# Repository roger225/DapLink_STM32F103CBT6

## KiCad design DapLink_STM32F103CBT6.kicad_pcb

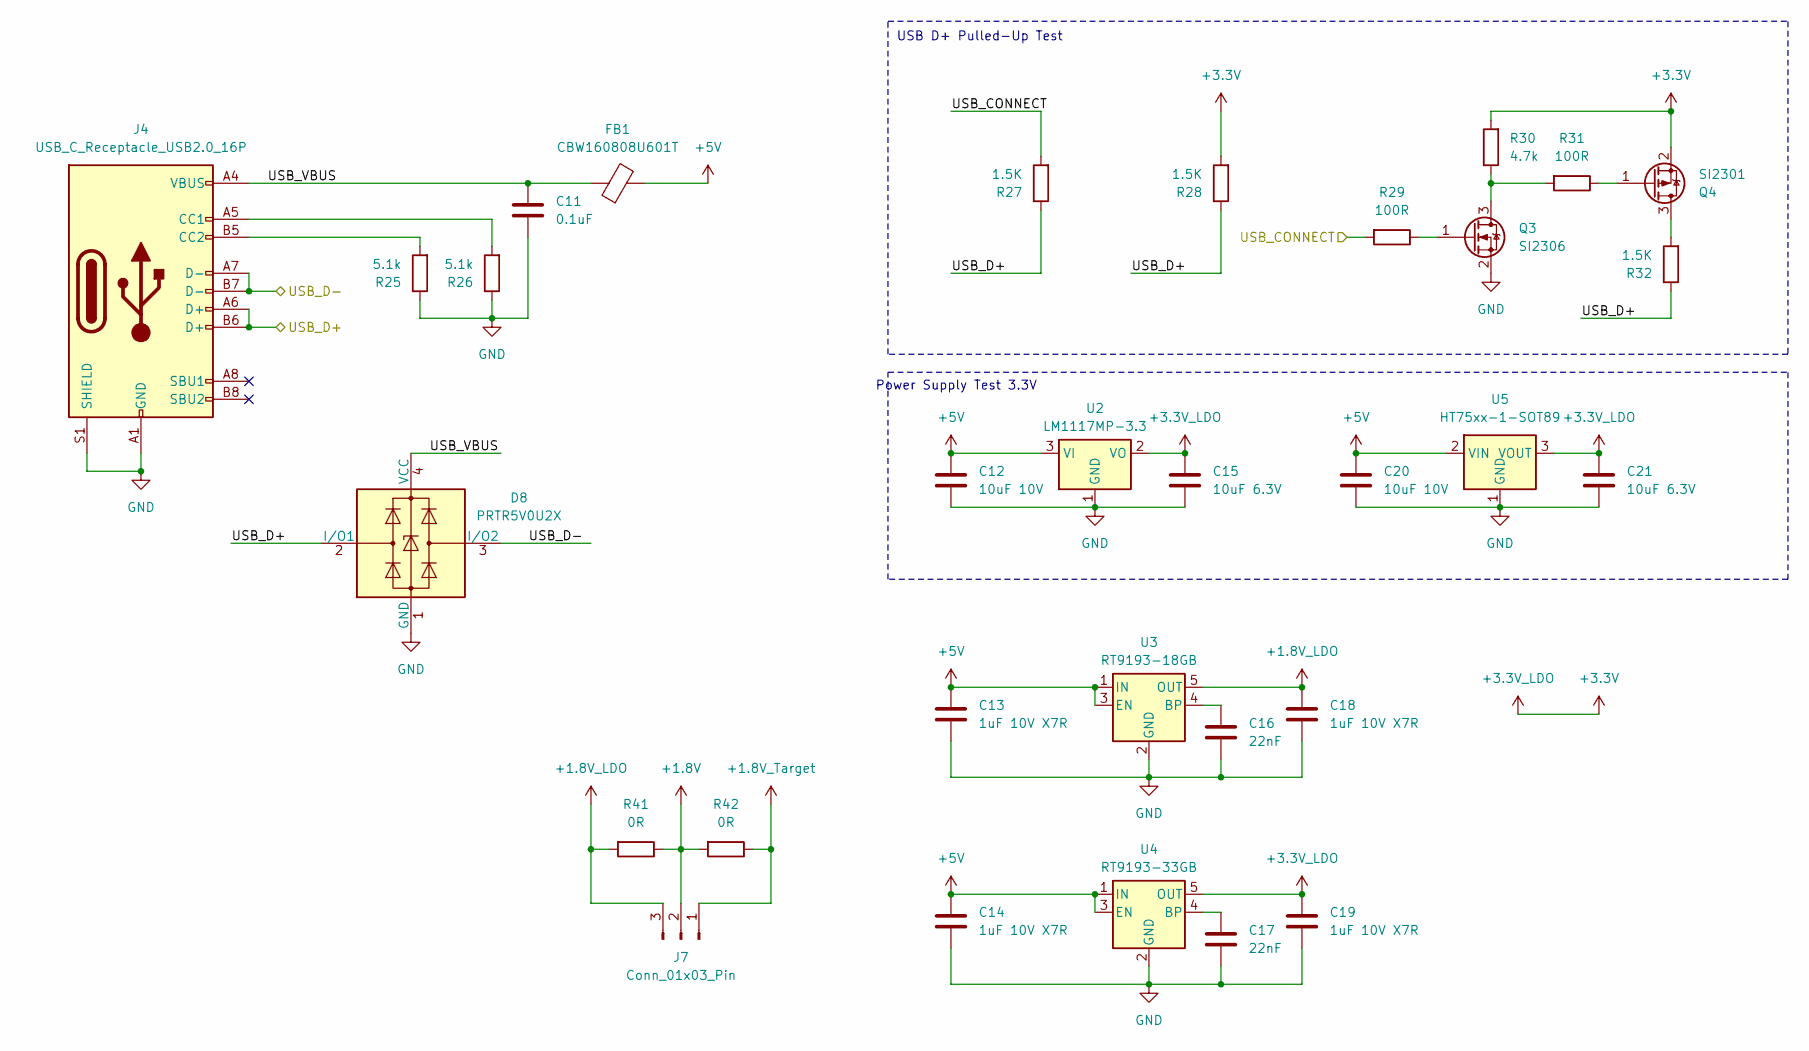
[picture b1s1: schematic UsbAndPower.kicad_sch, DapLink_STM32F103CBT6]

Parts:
C11: 0.1uF; C_0805_2012Metric
C12, C20: 10uF 10V; C_0805_2012Metric
C13, C14, C18, C19: 1uF 10V X7R; C_1206_3216Metric
C15, C21: 10uF 6.3V; C_0805_2012Metric
C16, C17: 22nF; C_0805_2012Metric
D8: PRTR5V0U2X; SOT-143
FB1: CBW160808U601T; L_0603_1608Metric
J4: USB_C_Receptacle_USB2.0_16P; USB_C_Receptacle_G-Switch_GT-USB-7010ASV
J7: Conn_01x03_Pin; PinHeader_1x03_P2.54mm_Vertical
Q3: SI2306; SOT-23
Q4: SI2301; SOT-23
R25, R26: 5.1k; R_0805_2012Metric
R27, R28, R32: 1.5K; R_0805_2012Metric
R29, R31: 100R; R_0805_2012Metric
R30: 4.7k; R_0805_2012Metric
R41, R42: 0R; R_0805_2012Metric
U2: LM1117MP-3.3; SOT-223-3_TabPin2
U3: RT9193-18GB; SOT-23-5
U4: RT9193-33GB; SOT-23-5
U5: HT75xx-1-SOT89; SOT-89-3

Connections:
+1.8V: J7.2, R41.1, R42.2; also elsewhere on the board
+1.8V_LDO: C18.1, J7.3, R41.2, U3.5 (OUT)
+1.8V_Target: J7.1, R42.1; also elsewhere on the board
+3.3V: C15.1, C19.1, C21.1, Q4.2 (S), R28.2, R30.2, U2.2 (VO), U4.5 (OUT), U5.3 (VOUT); also elsewhere on the board
+5V: C12.1, C13.1, C14.1, C20.1, FB1.2, U2.3 (VI), U3.1 (IN), U3.3 (EN), U4.1 (IN), U4.3 (EN), U5.2 (VIN)
/UsbAndPower/USB_CONNECT: R27.2, R29.2; also elsewhere on the board
/UsbAndPower/USB_D+: D8.2 (I/O1), J4.A6 (D+), J4.B6 (D+), R27.1, R28.1, R32.1; also elsewhere on the board
/UsbAndPower/USB_D-: D8.3 (I/O2), J4.A7 (D-), J4.B7 (D-); also elsewhere on the board
/UsbAndPower/USB_VBUS: C11.1, D8.4 (VCC), FB1.1, J4.A4 (VBUS), J4.A9 (VBUS), J4.B4 (VBUS), J4.B9 (VBUS)
GND: C11.2, C12.2, C13.2, C14.2, C15.2, C16.2, C17.2, C18.2, C19.2, C20.2, C21.2, D8.1 (GND), J4.A1 (GND), J4.A12 (GND), J4.B1 (GND), J4.B12 (GND), J4.S1 (SHIELD), Q3.2 (S), R25.1, R26.1, U2.1 (GND), U3.2 (GND), U4.2 (GND), U5.1 (GND); also elsewhere on the board
unnamed: J4.A5 (CC1), R26.2
unnamed: J4.B5 (CC2), R25.2
unnamed: Q3.3 (D), R30.1, R31.2
unnamed: Q3.1 (G), R29.1
unnamed: Q4.3 (D), R32.2
unnamed: Q4.1 (G), R31.1
unnamed: C16.1, U3.4 (BP)
unnamed: C17.1, U4.4 (BP)

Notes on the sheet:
Power Supply Test 3.3V
USB D+ Pulled-Up Test

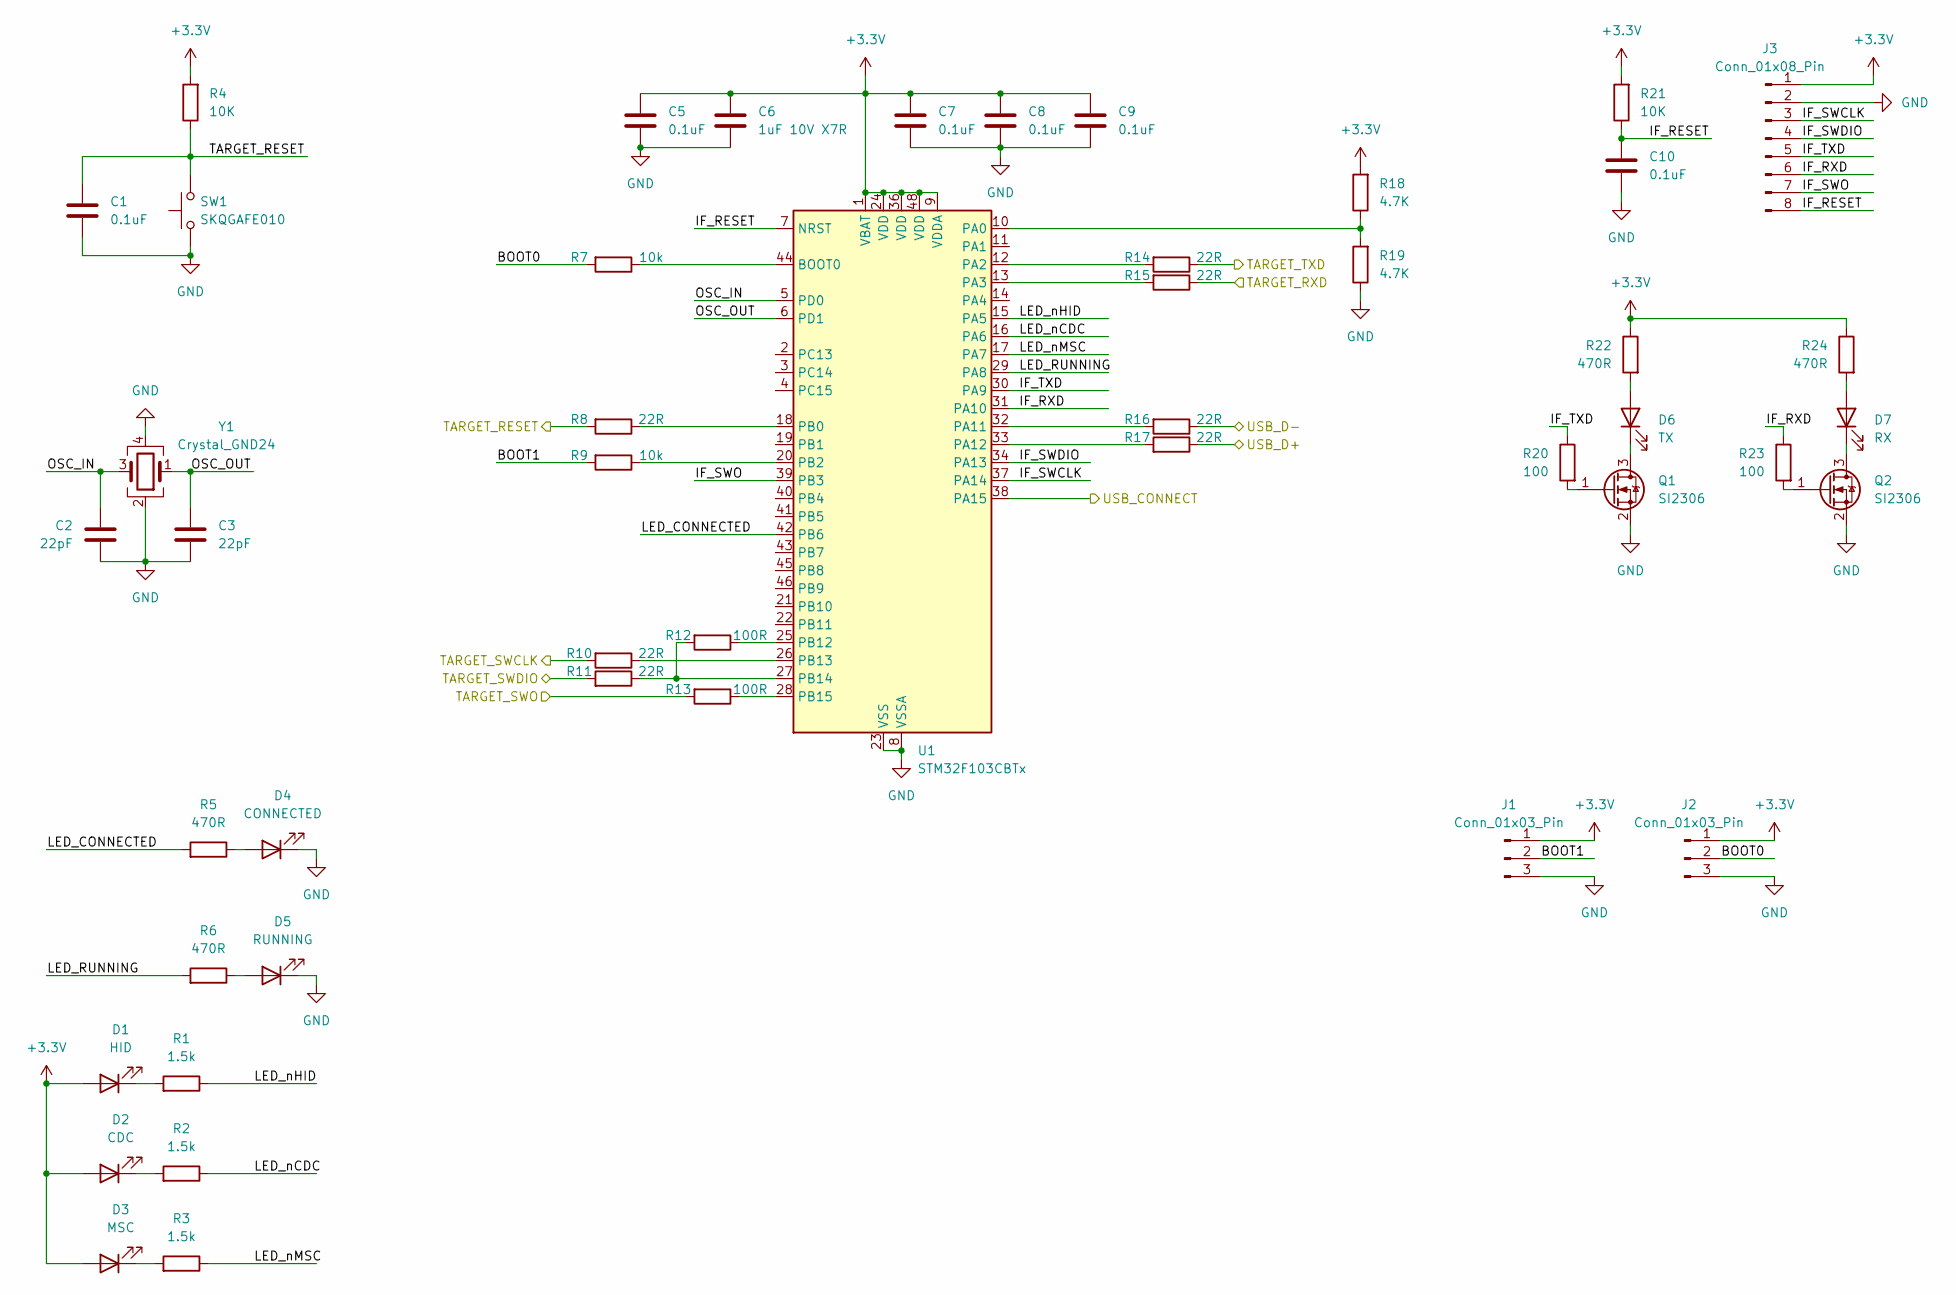
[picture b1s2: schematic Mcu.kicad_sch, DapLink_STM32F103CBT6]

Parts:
C1, C5, C7, C8, C9, C10: 0.1uF; C_0805_2012Metric
C2, C3: 22pF; C_0603_1608Metric
C6: 1uF 10V X7R; C_1206_3216Metric
D1: HID; LED_0805_2012Metric
D2: CDC; LED_0805_2012Metric
D3: MSC; LED_0805_2012Metric
D4: CONNECTED; LED_0805_2012Metric
D5: RUNNING; LED_0805_2012Metric
D6: TX; LED_0805_2012Metric
D7: RX; LED_0805_2012Metric
J1, J2: Conn_01x03_Pin; PinHeader_1x03_P2.54mm_Vertical
J3: Conn_01x08_Pin; PinHeader_1x08_P2.54mm_Vertical
Q1, Q2: SI2306; SOT-23
R1, R2, R3: 1.5k; R_0805_2012Metric
R4, R21: 10K; R_0805_2012Metric
R5, R6, R22, R24: 470R; R_0805_2012Metric
R7, R9: 10k; R_0805_2012Metric
R8, R10, R11, R14, R15, R16, R17: 22R; R_0805_2012Metric
R12, R13: 100R; R_0805_2012Metric
R18, R19: 4.7K; R_0805_2012Metric
R20, R23: 100; R_0805_2012Metric
SW1: SKQGAFE010; SW_SPST_SKQG_WithStem
U1: STM32F103CBTx; LQFP-48_7x7mm_P0.5mm
Y1: Crystal_GND24; Crystal_SMD_3225-4Pin_3.2x2.5mm

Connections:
+3.3V: C5.1, C6.1, C7.1, C8.1, C9.1, D1.2 (A), D2.2 (A), D3.2 (A), J1.1, J2.1, J3.1, R4.2, R18.2, R21.2, R22.1, R24.1, U1.1 (VBAT), U1.9 (VDDA), U1.24 (VDD), U1.36 (VDD), U1.48 (VDD); also elsewhere on the board
/DebugAndUart/TARGET_RESET: C1.1, R4.1, R8.2, SW1.2; also elsewhere on the board
/DebugAndUart/TARGET_RXD: R15.1; also elsewhere on the board
/DebugAndUart/TARGET_SWCLK: R10.2; also elsewhere on the board
/DebugAndUart/TARGET_SWDIO: R11.2; also elsewhere on the board
/DebugAndUart/TARGET_SWO: R13.2; also elsewhere on the board
/DebugAndUart/TARGET_TXD: R14.1; also elsewhere on the board
/Mcu/BOOT0: J2.2, R7.2
/Mcu/BOOT1: J1.2, R9.2
/Mcu/IF_RESET: C10.1, J3.8, R21.1, U1.7 (NRST)
/Mcu/IF_RXD: J3.6, R23.1, U1.31 (PA10)
/Mcu/IF_SWCLK: J3.3, U1.37 (PA14)
/Mcu/IF_SWDIO: J3.4, U1.34 (PA13)
/Mcu/IF_SWO: J3.7, U1.39 (PB3)
/Mcu/IF_TXD: J3.5, R20.1, U1.30 (PA9)
/Mcu/LED_CONNECTED: R5.2, U1.42 (PB6)
/Mcu/LED_RUNNING: R6.2, U1.29 (PA8)
/Mcu/LED_nCDC: R2.1, U1.16 (PA6)
/Mcu/LED_nHID: R1.1, U1.15 (PA5)
/Mcu/LED_nMSC: R3.1, U1.17 (PA7)
/Mcu/OSC_IN: C2.2, U1.5 (PD0), Y1.3
/Mcu/OSC_OUT: C3.1, U1.6 (PD1), Y1.1
/UsbAndPower/USB_CONNECT: U1.38 (PA15); also elsewhere on the board
/UsbAndPower/USB_D+: R17.1; also elsewhere on the board
/UsbAndPower/USB_D-: R16.1; also elsewhere on the board
GND: C1.2, C2.1, C3.2, C5.2, C6.2, C7.2, C8.2, C9.2, C10.2, D4.1 (K), D5.1 (K), J1.3, J2.3, J3.2, Q1.2 (S), Q2.2 (S), R19.1, SW1.1, U1.8 (VSSA), U1.23 (VSS), U1.35 (VSS), U1.47 (VSS), Y1.2, Y1.4; also elsewhere on the board
unnamed: D1.1 (K), R1.2
unnamed: D2.1 (K), R2.2
unnamed: D3.1 (K), R3.2
unnamed: D4.2 (A), R5.1
unnamed: D5.2 (A), R6.1
unnamed: D6.2 (A), R22.2
unnamed: D6.1 (K), Q1.3 (D)
unnamed: D7.2 (A), R24.2
unnamed: D7.1 (K), Q2.3 (D)
unnamed: Q1.1 (G), R20.2
unnamed: Q2.1 (G), R23.2
unnamed: R7.1, U1.44 (BOOT0)
unnamed: R18.1, R19.2, U1.10 (PA0)
unnamed: R14.2, U1.12 (PA2)
unnamed: R15.2, U1.13 (PA3)
unnamed: R16.2, U1.32 (PA11)
unnamed: R17.2, U1.33 (PA12)
unnamed: R8.1, U1.18 (PB0)
unnamed: R9.1, U1.20 (PB2)
unnamed: R12.1, U1.25 (PB12)
unnamed: R10.1, U1.26 (PB13)
unnamed: R11.1, R12.2, U1.27 (PB14)
unnamed: R13.1, U1.28 (PB15)

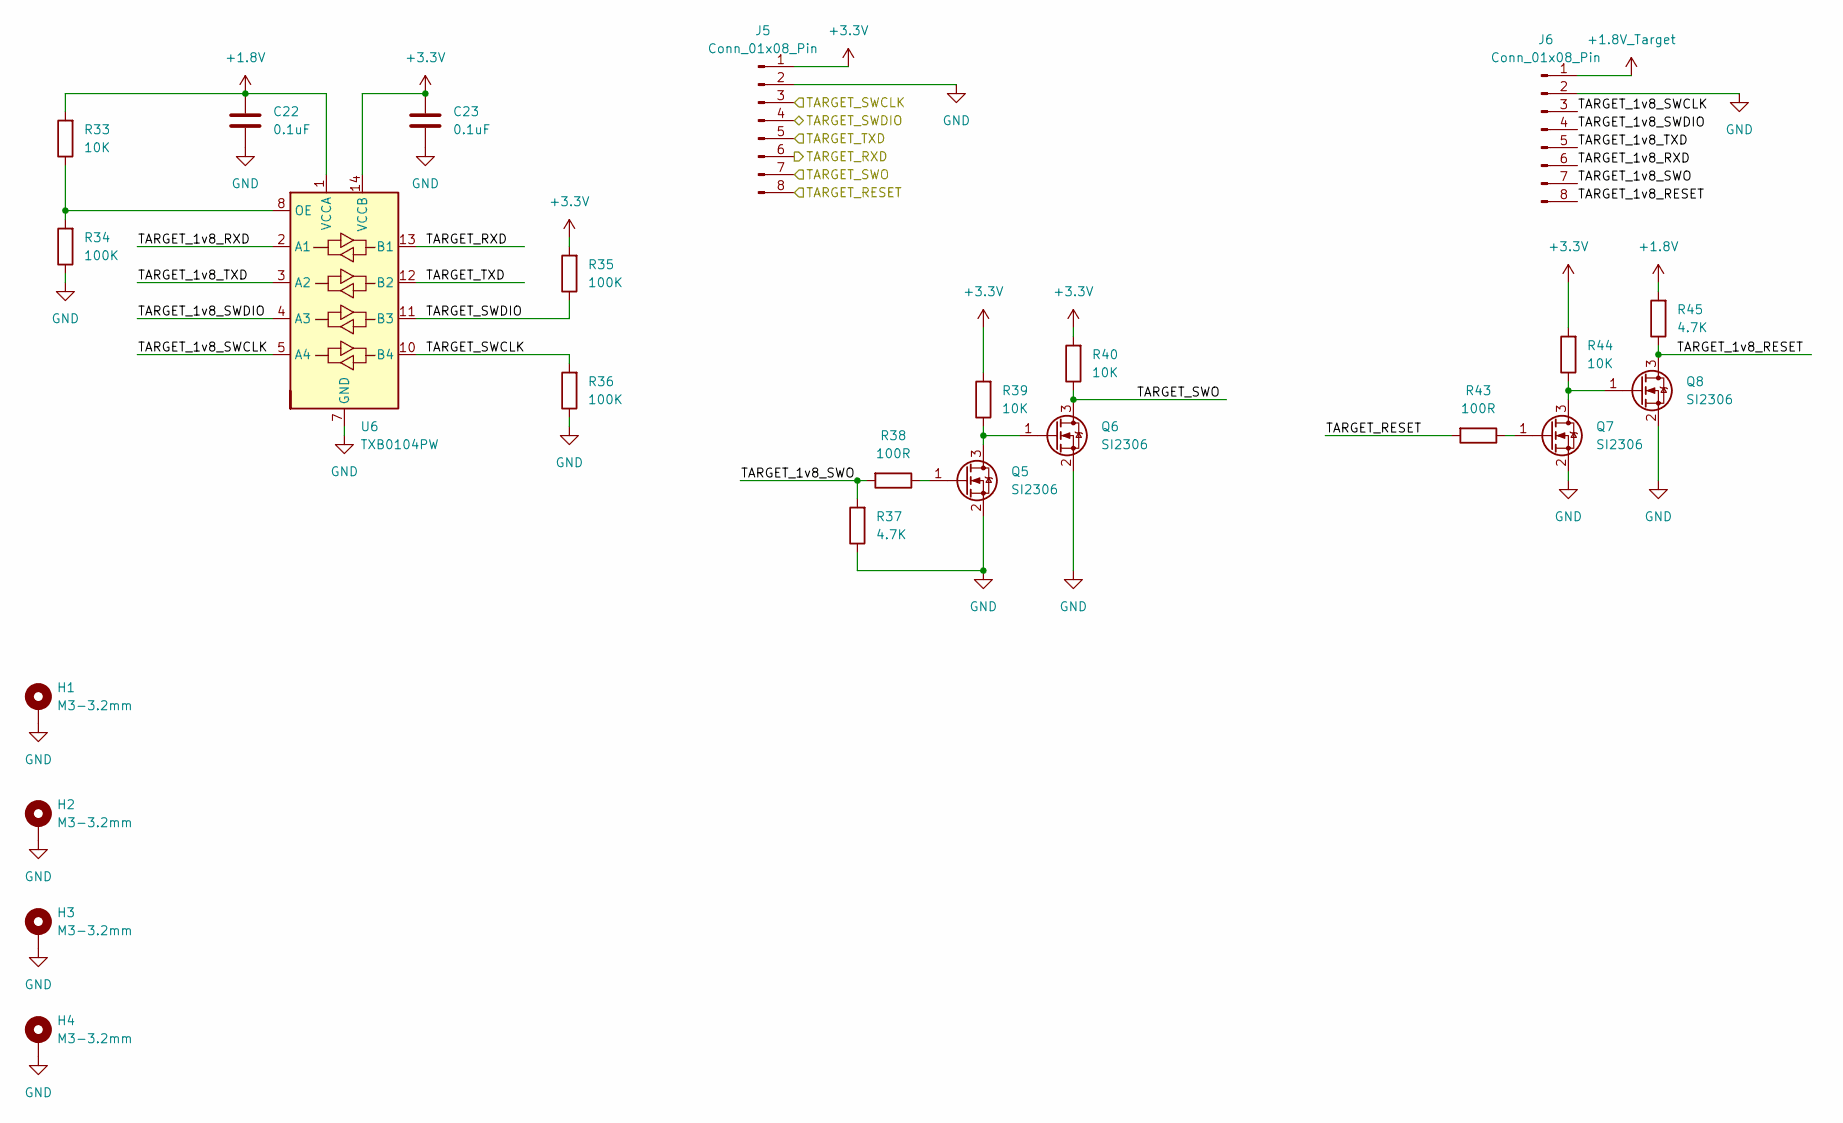
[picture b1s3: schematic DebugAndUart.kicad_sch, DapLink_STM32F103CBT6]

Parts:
C22, C23: 0.1uF; C_0805_2012Metric
H1, H2, H3, H4: M3-3.2mm; MountingHole_3.2mm_M3_Pad_Via
J5, J6: Conn_01x08_Pin; PinHeader_1x08_P2.54mm_Vertical
Q5, Q6, Q7, Q8: SI2306; SOT-23
R33, R39, R40, R44: 10K; R_0805_2012Metric
R34, R35, R36: 100K; R_0805_2012Metric
R37, R45: 4.7K; R_0805_2012Metric
R38, R43: 100R; R_0805_2012Metric
U6: TXB0104PW; TSSOP-14_4.4x5mm_P0.65mm

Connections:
+1.8V: C22.1, R33.2, R45.2, U6.1 (VCCA); also elsewhere on the board
+1.8V_Target: J6.1; also elsewhere on the board
+3.3V: C23.1, J5.1, R35.2, R39.2, R40.2, R44.2, U6.14 (VCCB); also elsewhere on the board
/DebugAndUart/TARGET_1v8_RESET: J6.8, Q8.3 (D), R45.1
/DebugAndUart/TARGET_1v8_RXD: J6.6, U6.2 (A1)
/DebugAndUart/TARGET_1v8_SWCLK: J6.3, U6.5 (A4)
/DebugAndUart/TARGET_1v8_SWDIO: J6.4, U6.4 (A3)
/DebugAndUart/TARGET_1v8_SWO: J6.7, R37.2, R38.2
/DebugAndUart/TARGET_1v8_TXD: J6.5, U6.3 (A2)
/DebugAndUart/TARGET_RESET: J5.8, R43.2; also elsewhere on the board
/DebugAndUart/TARGET_RXD: J5.6, U6.13 (B1); also elsewhere on the board
/DebugAndUart/TARGET_SWCLK: J5.3, R36.2, U6.10 (B4); also elsewhere on the board
/DebugAndUart/TARGET_SWDIO: J5.4, R35.1, U6.11 (B3); also elsewhere on the board
/DebugAndUart/TARGET_SWO: J5.7, Q6.3 (D), R40.1; also elsewhere on the board
/DebugAndUart/TARGET_TXD: J5.5, U6.12 (B2); also elsewhere on the board
GND: C22.2, C23.2, H1.1, H2.1, H3.1, H4.1, J5.2, J6.2, Q5.2 (S), Q6.2 (S), Q7.2 (S), Q8.2 (S), R34.1, R36.1, R37.1, U6.7 (GND); also elsewhere on the board
unnamed: Q5.3 (D), Q6.1 (G), R39.1
unnamed: Q5.1 (G), R38.1
unnamed: Q7.3 (D), Q8.1 (G), R44.1
unnamed: Q7.1 (G), R43.1
unnamed: R33.1, R34.2, U6.8 (OE)

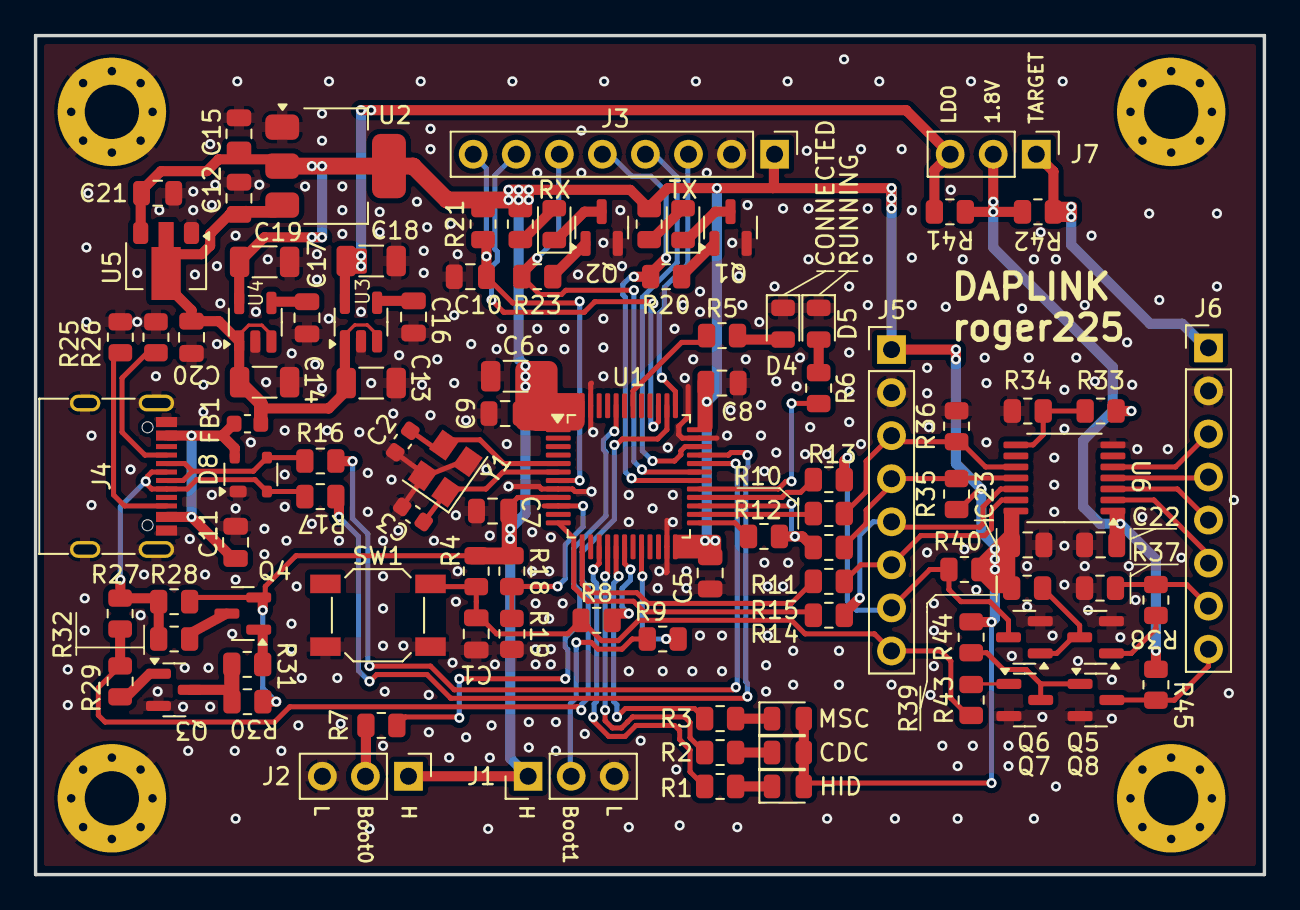
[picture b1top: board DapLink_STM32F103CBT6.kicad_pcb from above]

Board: 2 copper layers, 72.5 x 49.5 mm, 103 parts (0 on the bottom side), 73 nets.

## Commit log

2024-07-04 initial
2024-07-05 add temp reference
2024-07-07 TEMP
2024-07-08 3.3v power ok
2024-07-10 temp power
2024-07-11 add document
2024-07-21 reasonable placement for pcb
2024-07-23 temp gnd
2024-07-24 drc ok
2024-07-25 before rename led
2024-07-25 looks good v1
2024-07-27 fabrication v1
2024-08-18 modify F.SilkS for C20 and R26
